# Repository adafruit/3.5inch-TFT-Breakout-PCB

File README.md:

# Adafruit 3.5 inch TFT LCD Display Breakout PCB

<a href="http://www.adafruit.com/products/2050"><br/>
Click here to purchase one from the Adafruit shop</a>

<a href="http://www.adafruit.com/products/5846"><br/>
Click here to purchase one from the Adafruit shop</a>

Adafruit 3.5" 18-bit color TFT LCD display with microSD card breakout

This TFT display is big (3.5" diagonal) bright (6 white-LED backlight) and colorful! 480x320 pixels with individual RGB pixel control, this has way more resolution than a black and white 128x64 display, and double our 2.8" TFT. 

There are two version of this display: one has a resistive touchscreen attached to it and the other has a capacitive touchscreen attached.

This display has a controller built into it with RAM buffering, so that almost no work is done by the microcontroller. The display can be used in two modes: 8-bit or SPI. For 8-bit mode, you'll need 8 digital data lines and 4 or 5 digital control lines to read and write to the display (12 lines total). SPI mode requires only 5 pins total (SPI data in, data out, clock, select, and d/c) but is slower than 8-bit mode. In addition, 4 pins are required for the touch screen (2 digital, 2 analog) or you can purchase and use our resistive touchscreen controller (not included) to use I2C or SPI.

These are the Eagle CAD files for the Adafruit 3.5" 18-bit color TFT LCD display with microSD card breakout:
  ----> https://www.adafruit.com/products/2050

and the Adafruit 3.5" TFT 320x480 with Capacitive Touch Breakout Board - EYESPI
  ----> https://www.adafruit.com/products/5846

### License

Adafruit invests time and resources providing this open source design, please support Adafruit and open-source hardware by purchasing products from [Adafruit](https://www.adafruit.com)!

All text above must be included in any redistribution

Designed by Limor Fried/Ladyada for Adafruit Industries.
Creative Commons Attribution/Share-Alike, all text above must be included in any redistribution. 
See license.txt for additional information.

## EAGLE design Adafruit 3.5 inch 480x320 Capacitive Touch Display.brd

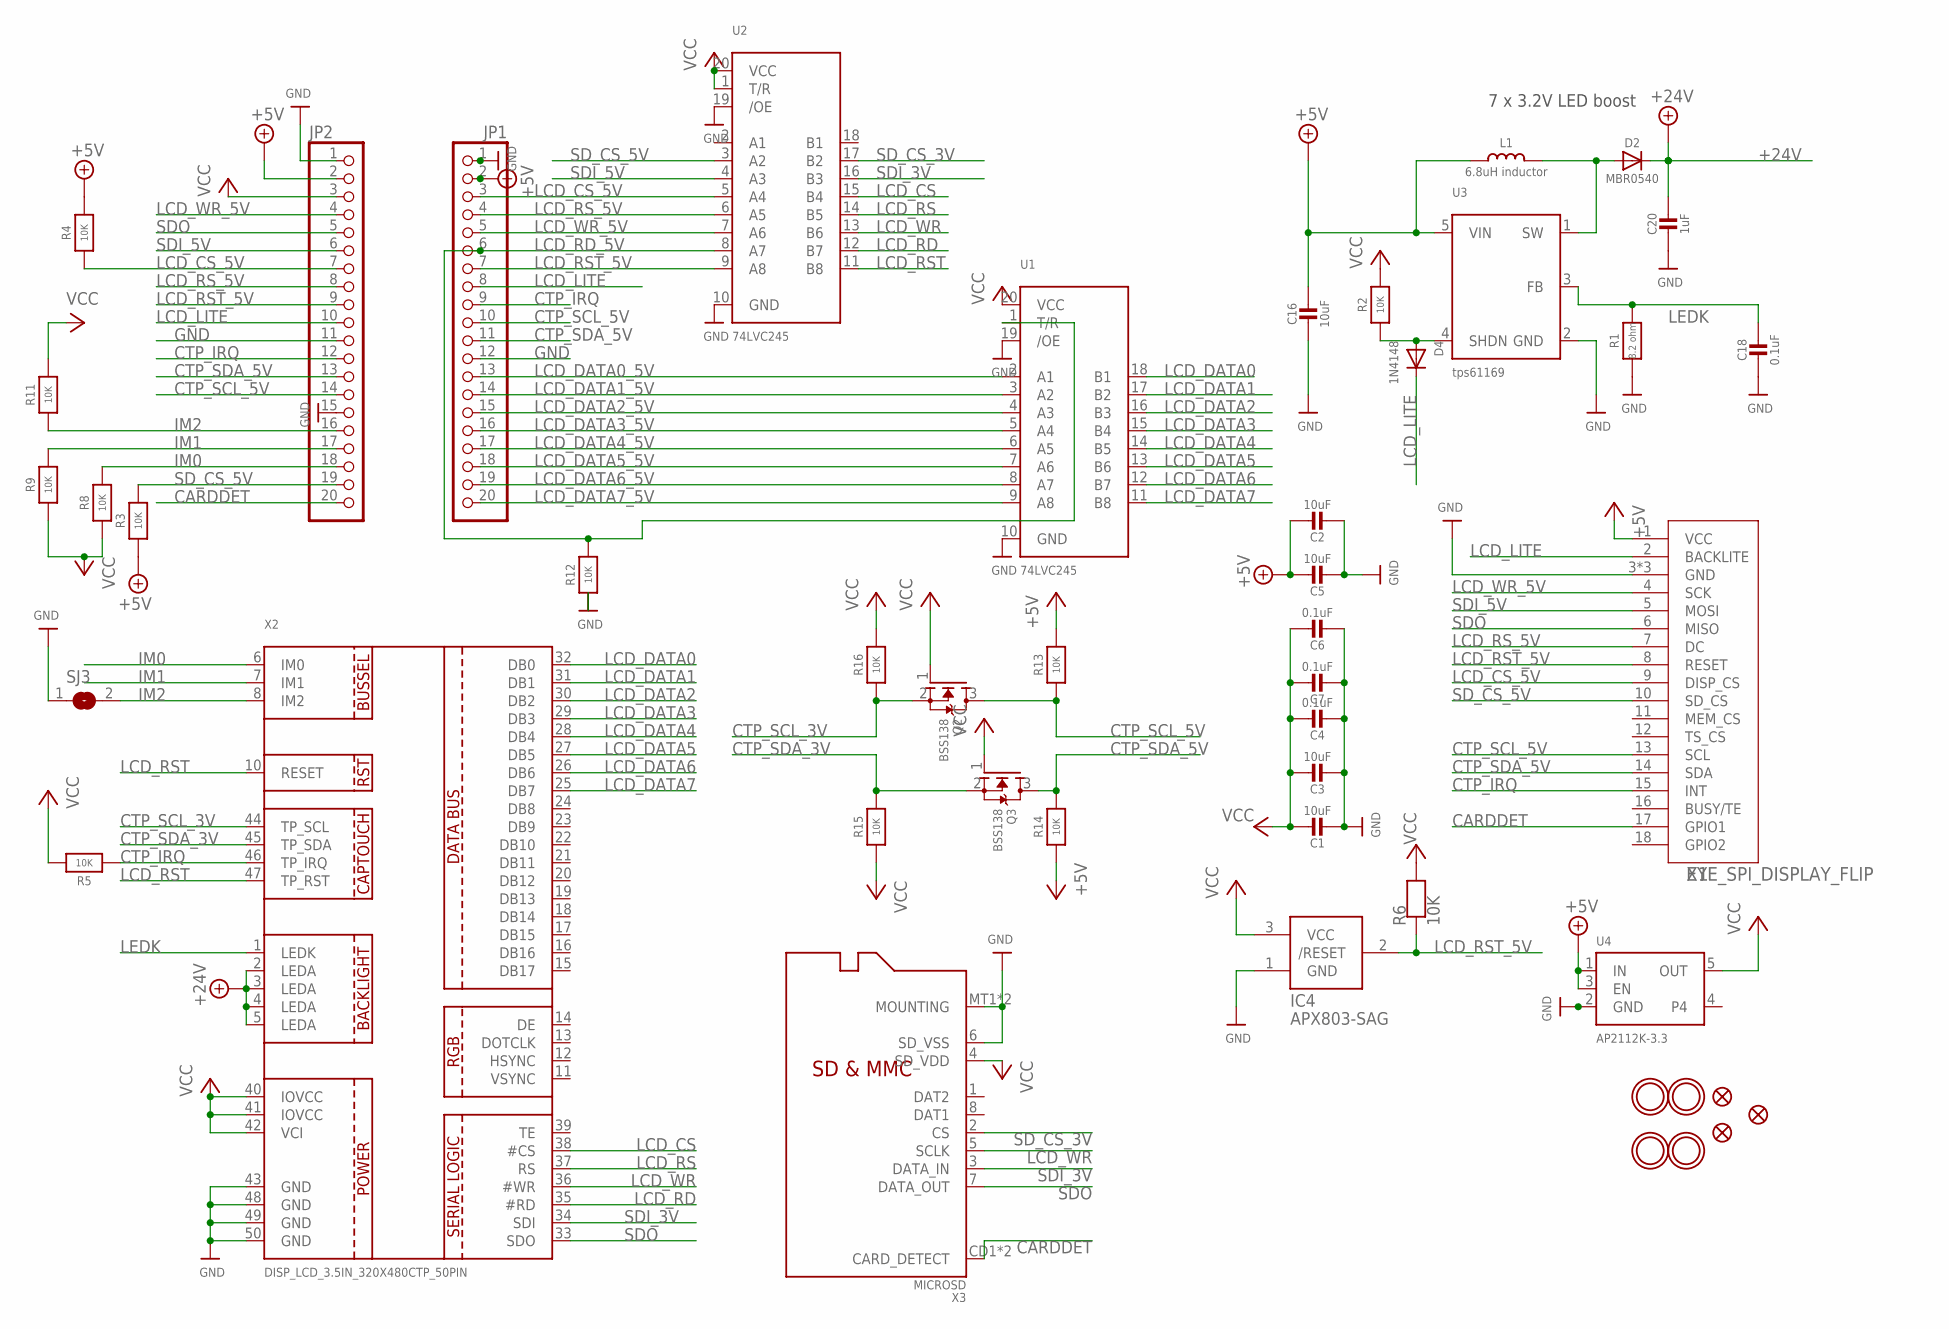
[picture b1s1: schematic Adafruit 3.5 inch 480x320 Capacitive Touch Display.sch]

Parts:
C1, C2, C3, C5, C16: 10uF; 0805-NO
C4, C6, C7, C18: 0.1uF; 0603-NO
C20: 1uF; 0805-NO
D2: MBR0540; SOD-123
D4: 1N4148; SOD-323F
IC4: APX803-SAG; SOT23
JP1, JP2: HEADER-1X20ROUND; 1X20_ROUND
L1: 6.8uH inductor; INDUCTOR_5X5MM_NR5040_NOTHERMALS
Q2, Q3: BSS138; SOT23-WIDE
R1: 8.2 ohm; 0603-NO
R2, R3, R4, R5, R6, R8, R9, R11, R12, R13, R14, R15, R16: 10K; 0603-NO
SJ3: SOLDERJUMPER; SOLDERJUMPER_ARROW_NOPASTE
U1, U2: 74LVC245; TSSOP20
U3: tps61169; SC70-5
U4: AP2112K-3.3; SOT23-5
U$7, U$15, U$16, U$17: MOUNTINGHOLE3.0THIN; MOUNTINGHOLE_3.0_PLATEDTHIN
U$9, U$11, U$23: FIDUCIAL_1MM
X1: EYE_SPI_DISPLAY_FLIP; EYE_SPI_DISPLAY_BOTCONTACT
X2: DISP_LCD_3.5IN_320X480CTP_50PIN; TFT_3.5IN_320X480_50PIN
X3: MICROSD

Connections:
+5V: C2.1, C5.1, C16.1, JP1.2, JP2.2, L1.P$1 (1), R3.1, R4.2, R13.2, R14.1, U3.5 (VIN), U4.1 (IN), U4.3 (EN), X1.1 (VCC)
+24V: C20.1, D2.C, X2.2 (LEDA), X2.3 (LEDA), X2.4 (LEDA), X2.5 (LEDA)
CARDDET: JP2.20, X1.17 (GPIO1), X3.CD1 (CARD_DETECT), X3.CD2 (CARD_DETECT)
CTP_IRQ: JP1.9, JP2.12, R5.1, X1.15 (INT), X2.46 (TP_IRQ)
CTP_SCL_3V: Q2.2 (S), R16.1, X2.44 (TP_SCL)
CTP_SCL_5V: JP1.10, JP2.14, Q2.3 (D), R13.1, X1.13 (SCL)
CTP_SDA_3V: Q3.2 (S), R15.2, X2.45 (TP_SDA)
CTP_SDA_5V: JP1.11, JP2.13, Q3.3 (D), R14.2, X1.14 (SDA)
GND: C1.2, C2.2, C3.2, C4.2, C5.2, C6.2, C7.2, C16.2, C18.2, C20.2, IC4.1 (GND), JP1.1, JP1.12, JP2.1, JP2.11, JP2.15, R1.1, R12.1, SJ3.1, U1.10 (GND), U1.19 (/OE), U2.10 (GND), U2.19 (/OE), U3.2 (GND), U4.2 (GND), X1.3 (GND), X1.SUPPORT1 (GND), X1.SUPPORT2 (GND), X2.43 (GND), X2.48 (GND), X2.49 (GND), X2.50 (GND), X3.6 (SD_VSS), X3.MT1 (MOUNTING), X3.MT2 (MOUNTING)
IM0: JP2.18, R8.2, X2.6 (IM0)
IM1: JP2.17, R9.2, X2.7 (IM1)
IM2: JP2.16, R11.1, SJ3.2, X2.8 (IM2)
LCD_CS: U2.15 (B4), X2.38 (#CS)
LCD_CS_5V: JP1.3, JP2.7, R4.1, U2.5 (A4), X1.9 (DISP_CS)
LCD_DATA0: U1.18 (B1), X2.32 (DB0)
LCD_DATA0_5V: JP1.13, U1.2 (A1)
LCD_DATA1: U1.17 (B2), X2.31 (DB1)
LCD_DATA1_5V: JP1.14, U1.3 (A2)
LCD_DATA2: U1.16 (B3), X2.30 (DB2)
LCD_DATA2_5V: JP1.15, U1.4 (A3)
LCD_DATA3: U1.15 (B4), X2.29 (DB3)
LCD_DATA3_5V: JP1.16, U1.5 (A4)
LCD_DATA4: U1.14 (B5), X2.28 (DB4)
LCD_DATA4_5V: JP1.17, U1.6 (A5)
LCD_DATA5: U1.13 (B6), X2.27 (DB5)
LCD_DATA5_5V: JP1.18, U1.7 (A6)
LCD_DATA6: U1.12 (B7), X2.26 (DB6)
LCD_DATA6_5V: JP1.19, U1.8 (A7)
LCD_DATA7: U1.11 (B8), X2.25 (DB7)
LCD_DATA7_5V: JP1.20, U1.9 (A8)
LCD_LITE: D4.C, JP1.8, JP2.10, X1.2 (BACKLITE)
LCD_RD: U2.12 (B7), X2.35 (#RD)
LCD_RD_5V: JP1.6, R12.2, U1.1 (T/R), U2.8 (A7)
LCD_RS: U2.14 (B5), X2.37 (RS)
LCD_RST: U2.11 (B8), X2.10 (RESET), X2.47 (TP_RST)
LCD_RST_5V: IC4.2 (/RESET), JP1.7, JP2.9, R6.1, U2.9 (A8), X1.8 (RESET)
LCD_RS_5V: JP1.4, JP2.8, U2.6 (A5), X1.7 (DC)
LCD_WR: U2.13 (B6), X2.36 (#WR), X3.5 (SCLK)
LCD_WR_5V: JP1.5, JP2.4, U2.7 (A6), X1.4 (SCK)
LEDK: C18.1, R1.2, U3.3 (FB), X2.1 (LEDK)
unnamed: D2.A, L1.P$2 (2), U3.1 (SW)
SDI_3V: U2.16 (B3), X2.34 (SDI), X3.3 (DATA_IN)
SDI_5V: JP2.6, U2.4 (A3), X1.5 (MOSI)
SDO: JP2.5, X1.6 (MISO), X2.33 (SDO), X3.7 (DATA_OUT)
SD_CS_3V: U2.17 (B2), X3.2 (CS)
SD_CS_5V: JP2.19, R3.2, U2.3 (A2), X1.10 (SD_CS)
SHDN: D4.A, R2.1, U3.4 (SHDN)
VCC: C1.1, C3.1, C4.1, C6.1, C7.1, IC4.3 (VCC), JP2.3, Q2.1 (G), Q3.1 (G), R2.2, R5.2, R6.2, R8.1, R9.1, R11.2, R15.1, R16.2, U1.20 (VCC), U2.1 (T/R), U2.20 (VCC), U4.5 (OUT), X2.40 (IOVCC), X2.41 (IOVCC), X2.42 (VCI), X3.4 (SD_VDD)

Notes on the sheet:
7 x 3.2V LED boost

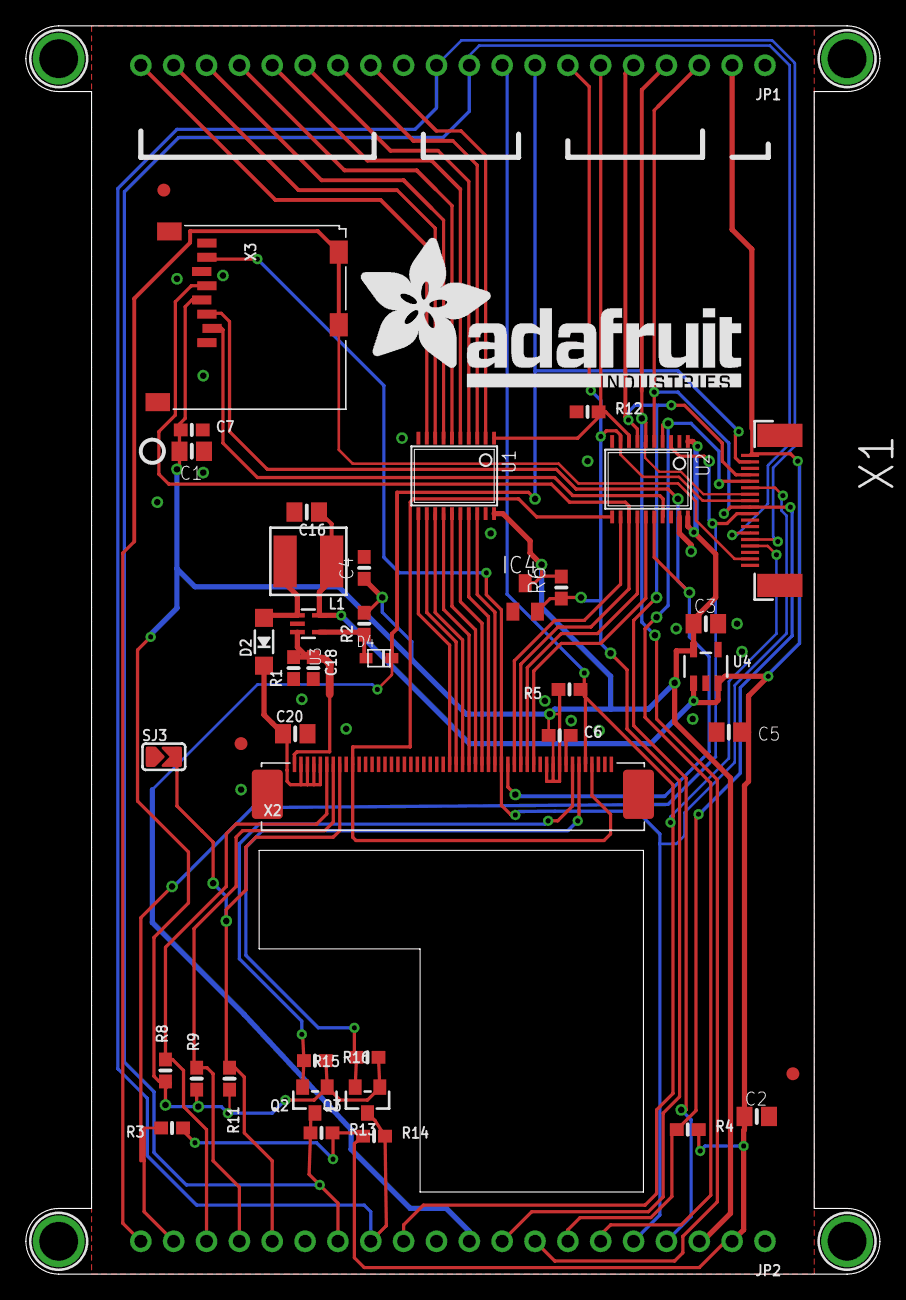
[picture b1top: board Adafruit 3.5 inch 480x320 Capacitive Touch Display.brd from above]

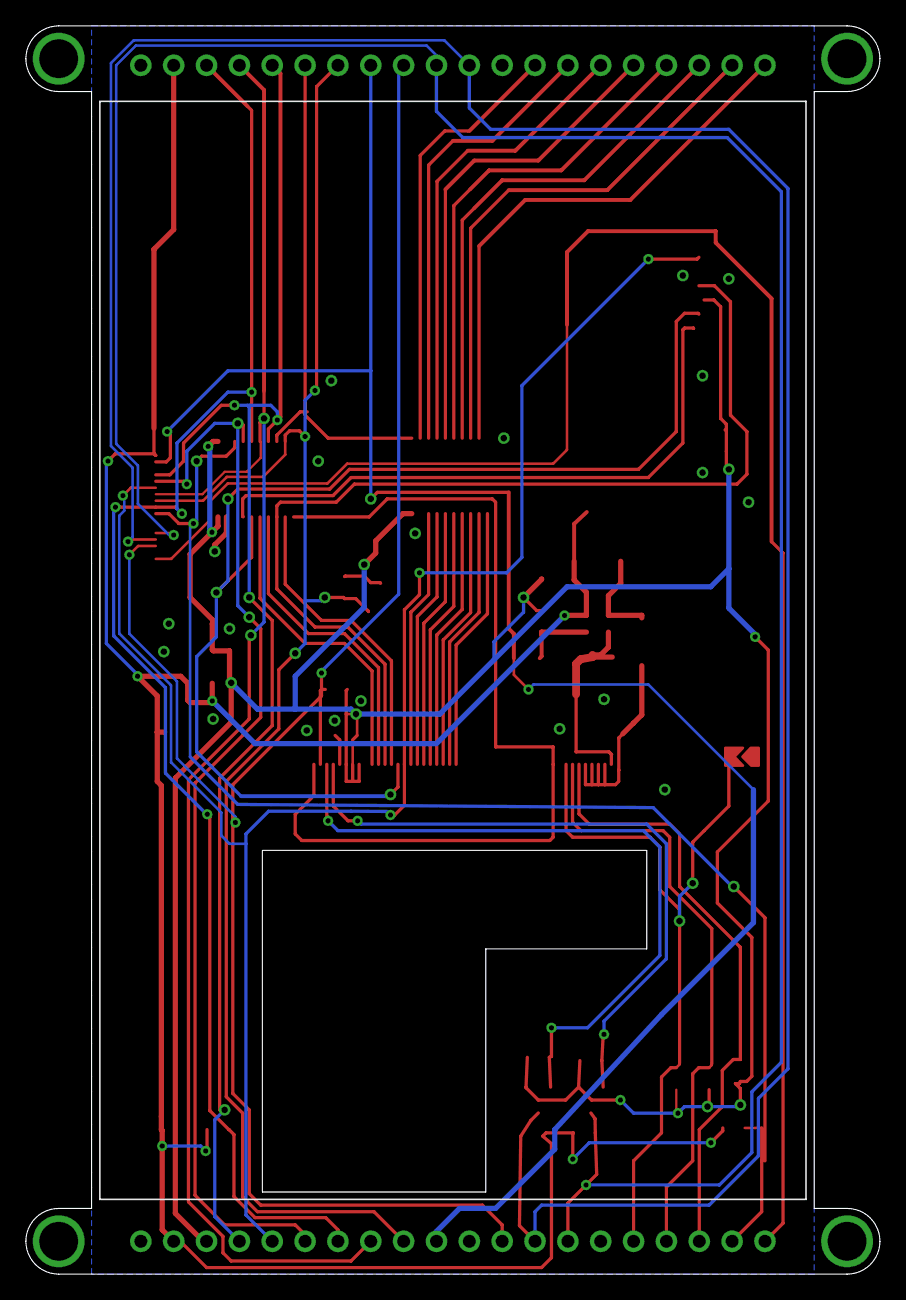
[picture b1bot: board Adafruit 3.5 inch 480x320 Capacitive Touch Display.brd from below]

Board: 2 copper layers, 66.0 x 96.5 mm, 143 parts (41 on the bottom side), 48 nets.

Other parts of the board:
PLABEL0: PLABEL0
PLABEL1: PLABEL1
PLABEL2: PLABEL2
PLABEL3: PLABEL3
PLABEL4: PLABEL4
PLABEL5: PLABEL5
PLABEL6: PLABEL6
PLABEL7: PLABEL7
PLABEL8: PLABEL8
PLABEL9: PLABEL9
PLABEL10: PLABEL10
PLABEL11: PLABEL11
PLABEL12: PLABEL12
PLABEL13: PLABEL13
PLABEL14: PLABEL14
PLABEL15: PLABEL15
PLABEL16: PLABEL16
PLABEL17: PLABEL17
PLABEL18: PLABEL18
PLABEL19: PLABEL19
PLABEL20: PLABEL20
PLABEL21: PLABEL21
PLABEL22: PLABEL22
PLABEL23: PLABEL23
PLABEL24: PLABEL24
PLABEL25: PLABEL25
PLABEL26: PLABEL26
PLABEL27: PLABEL27
PLABEL28: PLABEL28
PLABEL29: PLABEL29
PLABEL30: PLABEL30
PLABEL31: PLABEL31
PLABEL32: PLABEL32
PLABEL33: PLABEL33
PLABEL34: PLABEL34
PLABEL35: PLABEL35
PLABEL36: PLABEL36
PLABEL37: PLABEL37
PLABEL38: PLABEL38
PLABEL39: PLABEL39
PLABEL40: PLABEL40
PLABEL41: PLABEL41
PLABEL42: PLABEL42
PLABEL43: PLABEL43
PLABEL44: PLABEL44
PLABEL45: PLABEL45
PLABEL46: PLABEL46
PLABEL47: PLABEL47
PLABEL48: PLABEL48
PLABEL49: PLABEL49
PLABEL50: PLABEL50
PLABEL51: PLABEL51
PLABEL52: PLABEL52
PLABEL53: PLABEL53
PLABEL54: PLABEL54
PLABEL55: PLABEL55
PLABEL56: PLABEL56
PLABEL57: PLABEL57
PLABEL58: PLABEL58
PLABEL59: PLABEL59
PLABEL60: PLABEL60
PLABEL61: PLABEL61
PLABEL62: PLABEL62
PLABEL63: PLABEL63
PLABEL64: PLABEL64
PLABEL65: PLABEL65
PLABEL66: PLABEL66
PLABEL67: PLABEL67
PLABEL68: PLABEL68
PLABEL69: PLABEL69
PLABEL70: PLABEL70
PLABEL71: PLABEL71
PLABEL72: PLABEL72
PLABEL73: PLABEL73
PLABEL74: PLABEL74
PLABEL75: PLABEL75
PLABEL76: PLABEL76
PLABEL77: PLABEL77
PLABEL78: PLABEL78
PLABEL79: PLABEL79
PLABEL80: PLABEL80
PLABEL81: PLABEL81
PLABEL82: PLABEL82
PLABEL83: PLABEL83
PLABEL84: PLABEL84
PLABEL85: PLABEL85
PLABEL86: PLABEL86
PLABEL87: PLABEL87
PLABEL88: PLABEL88
PLABEL89: PLABEL89
PLABEL90: PLABEL90
PLABEL91: PLABEL91
PLABEL92: PLABEL92
PLABEL93: PLABEL93
U$19: ADAFRUIT_TEXT_30MM
U$31: PCBFEAT-REV-040

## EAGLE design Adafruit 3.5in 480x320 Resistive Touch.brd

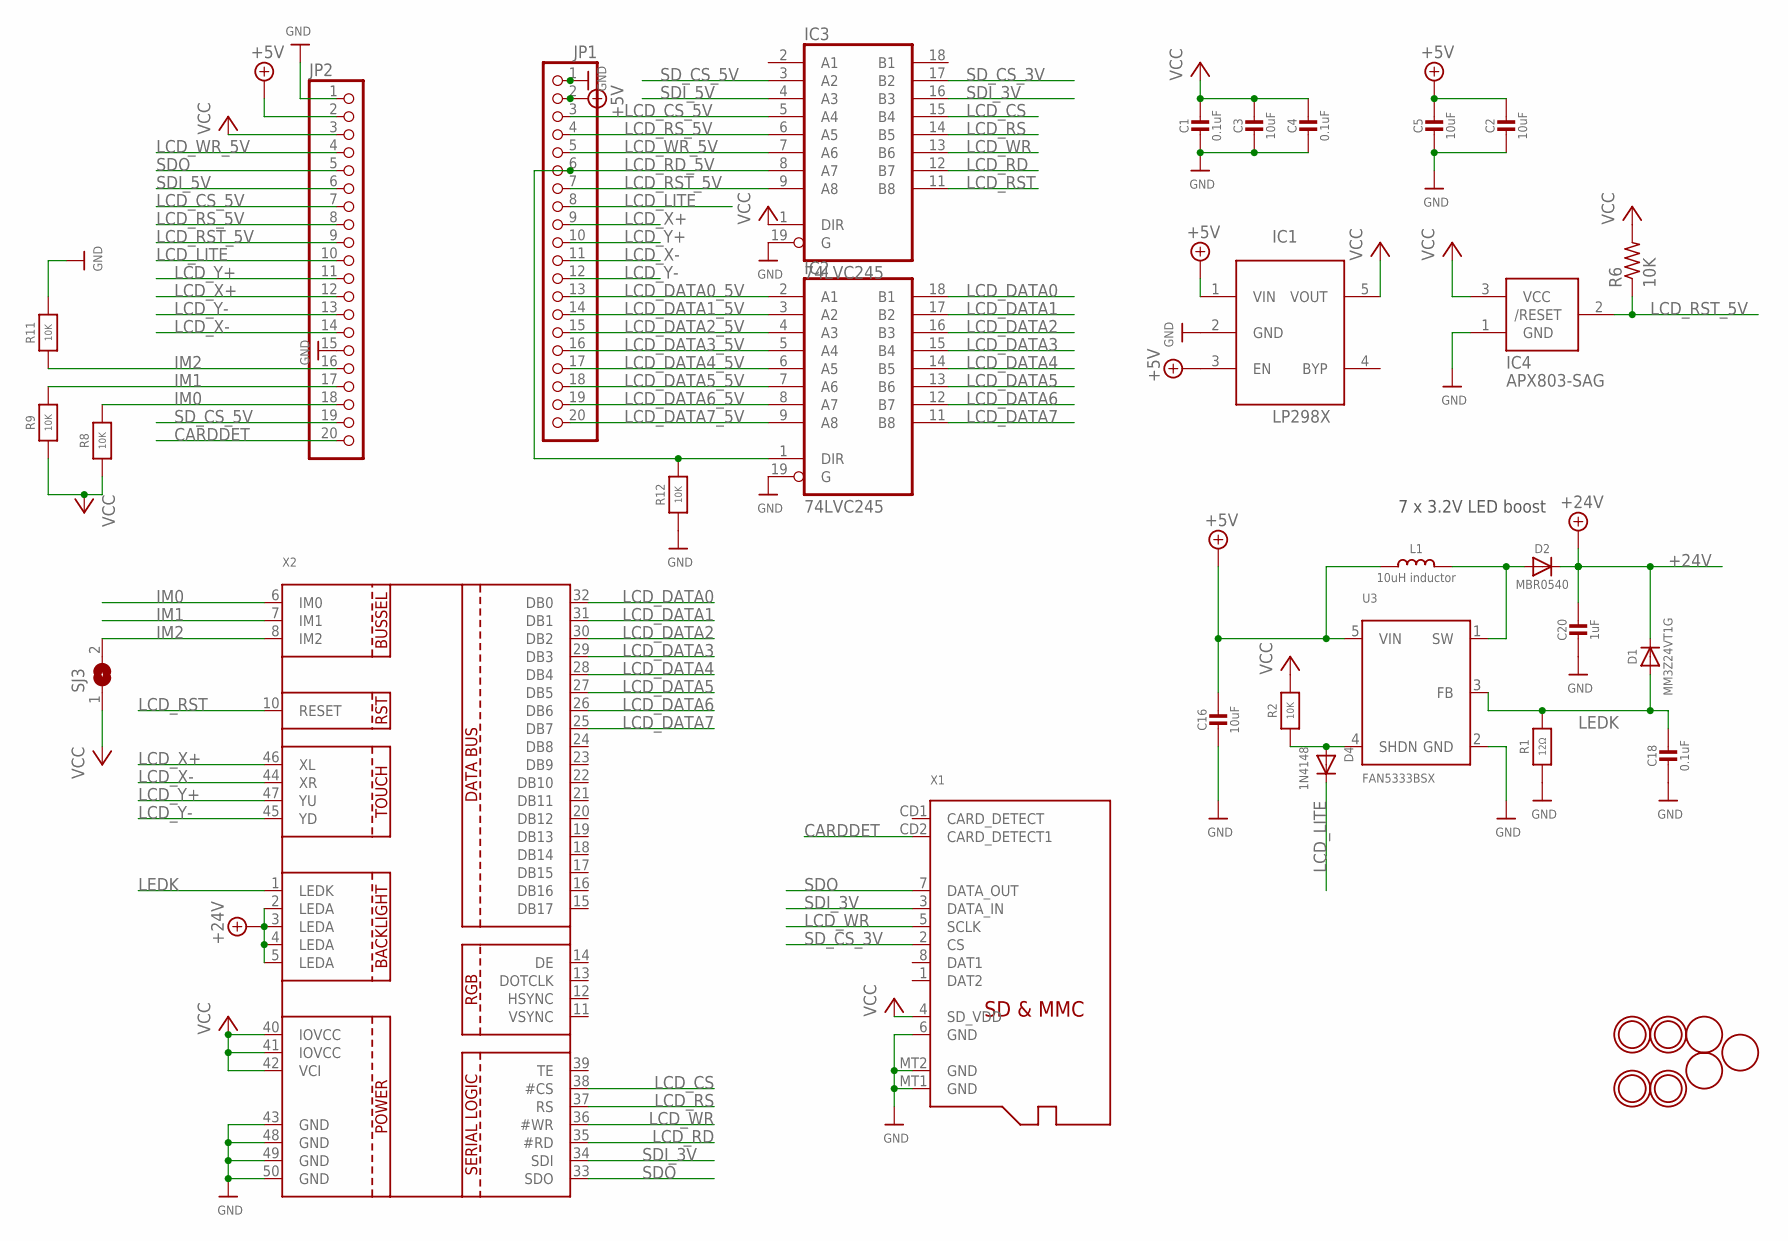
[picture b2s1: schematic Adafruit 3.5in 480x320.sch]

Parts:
C1, C4, C18: 0.1uF; 0805-NO
C2, C3, C5: 10uF; 0805-NO
C16: 10uF; _0805MP
C20: 1uF; 0805-NO
D1: MM3Z24VT1G; SMADIODE
D2: MBR0540; SOD-123
D4: 1N4148; SOD-323F
IC1: MIC5225-3.3; SOT23-5L
IC2, IC3: 74LVC245; SO20W
IC4: APX803-SAG; SOT23
JP1, JP2: HEADER-1X20ROUND; 1X20_ROUND
L1: 10uH inductor; INDUCTOR_5X5MM_NR5040_NOTHERMALS
R1: 12Ω; _0805MP
R2, R8, R9, R11, R12: 10K; 0805-NO
R6: 10K; R0805
SJ3: SOLDERJUMPER; SOLDERJUMPER_ARROW_NOPASTE
U3: FAN5333BSX; SOT23-5@1
U$7, U$15, U$16, U$17: MOUNTINGHOLE3.0THIN; MOUNTINGHOLE_3.0_PLATEDTHIN
U$9, U$11, U$23: FIDUCIAL; FIDUCIAL_1MM
X1: MICROSD
X2: DISP_LCD_3.5IN_320X480_50PIN; TFT_3.5IN_320X480_50PIN

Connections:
+5V: C2.1, C5.1, C16.1, IC1.1 (VIN), IC1.3 (EN), JP1.2, JP2.2, L1.P$1 (1), U3.5 (VIN)
+24V: C20.1, D1.C, D2.C, X2.2 (LEDA), X2.3 (LEDA), X2.4 (LEDA), X2.5 (LEDA)
CARDDET: JP2.20, X1.CD2 (CARD_DETECT1)
GND: C1.2, C2.2, C3.2, C4.2, C5.2, C16.2, C18.2, C20.2, IC1.2 (GND), IC2.10 (GND), IC2.19 (G), IC3.10 (GND), IC3.19 (G), IC4.1 (GND), JP1.1, JP2.1, JP2.15, R1.1, R11.2, R12.1, U3.2 (GND), X1.6 (GND), X1.MT1 (GND), X1.MT2 (GND), X2.43 (GND), X2.48 (GND), X2.49 (GND), X2.50 (GND)
IM0: JP2.18, R8.2, X2.6 (IM0)
IM1: JP2.17, R9.2, X2.7 (IM1)
IM2: JP2.16, R11.1, SJ3.2, X2.8 (IM2)
LCD_CS: IC3.15 (B4), X2.38 (#CS)
LCD_CS_5V: IC3.5 (A4), JP1.3, JP2.7
LCD_DATA0: IC2.18 (B1), X2.32 (DB0)
LCD_DATA0_5V: IC2.2 (A1), JP1.13
LCD_DATA1: IC2.17 (B2), X2.31 (DB1)
LCD_DATA1_5V: IC2.3 (A2), JP1.14
LCD_DATA2: IC2.16 (B3), X2.30 (DB2)
LCD_DATA2_5V: IC2.4 (A3), JP1.15
LCD_DATA3: IC2.15 (B4), X2.29 (DB3)
LCD_DATA3_5V: IC2.5 (A4), JP1.16
LCD_DATA4: IC2.14 (B5), X2.28 (DB4)
LCD_DATA4_5V: IC2.6 (A5), JP1.17
LCD_DATA5: IC2.13 (B6), X2.27 (DB5)
LCD_DATA5_5V: IC2.7 (A6), JP1.18
LCD_DATA6: IC2.12 (B7), X2.26 (DB6)
LCD_DATA6_5V: IC2.8 (A7), JP1.19
LCD_DATA7: IC2.11 (B8), X2.25 (DB7)
LCD_DATA7_5V: IC2.9 (A8), JP1.20
LCD_LITE: D4.C, JP1.8, JP2.10
LCD_RD: IC3.12 (B7), X2.35 (#RD)
LCD_RD_5V: IC2.1 (DIR), IC3.8 (A7), JP1.6, R12.2
LCD_RS: IC3.14 (B5), X2.37 (RS)
LCD_RST: IC3.11 (B8), X2.10 (RESET)
LCD_RST_5V: IC3.9 (A8), IC4.2 (/RESET), JP1.7, JP2.9, R6.1
LCD_RS_5V: IC3.6 (A5), JP1.4, JP2.8
LCD_WR: IC3.13 (B6), X1.5 (SCLK), X2.36 (#WR)
LCD_WR_5V: IC3.7 (A6), JP1.5, JP2.4
LCD_X+: JP1.9, JP2.12, X2.46 (XL)
LCD_X-: JP1.11, JP2.14, X2.44 (XR)
LCD_Y+: JP1.10, JP2.11, X2.47 (YU)
LCD_Y-: JP1.12, JP2.13, X2.45 (YD)
LEDK: C18.1, D1.A, R1.2, U3.3 (FB), X2.1 (LEDK)
unnamed: D2.A, L1.P$2 (2), U3.1 (SW)
SDI_3V: IC3.16 (B3), X1.3 (DATA_IN), X2.34 (SDI)
SDI_5V: IC3.4 (A3), JP2.6
SDO: JP2.5, X1.7 (DATA_OUT), X2.33 (SDO)
SD_CS_3V: IC3.17 (B2), X1.2 (CS)
SD_CS_5V: IC3.3 (A2), JP2.19
SHDN: D4.A, R2.1, U3.4 (SHDN)
VCC: C1.1, C3.1, C4.1, IC1.5 (VOUT), IC2.20 (VCC), IC3.1 (DIR), IC3.20 (VCC), IC4.3 (VCC), JP2.3, R2.2, R6.2, R8.1, R9.1, SJ3.1, X1.4 (SD_VDD), X2.40 (IOVCC), X2.41 (IOVCC), X2.42 (VCI)

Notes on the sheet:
7 x 3.2V LED boost

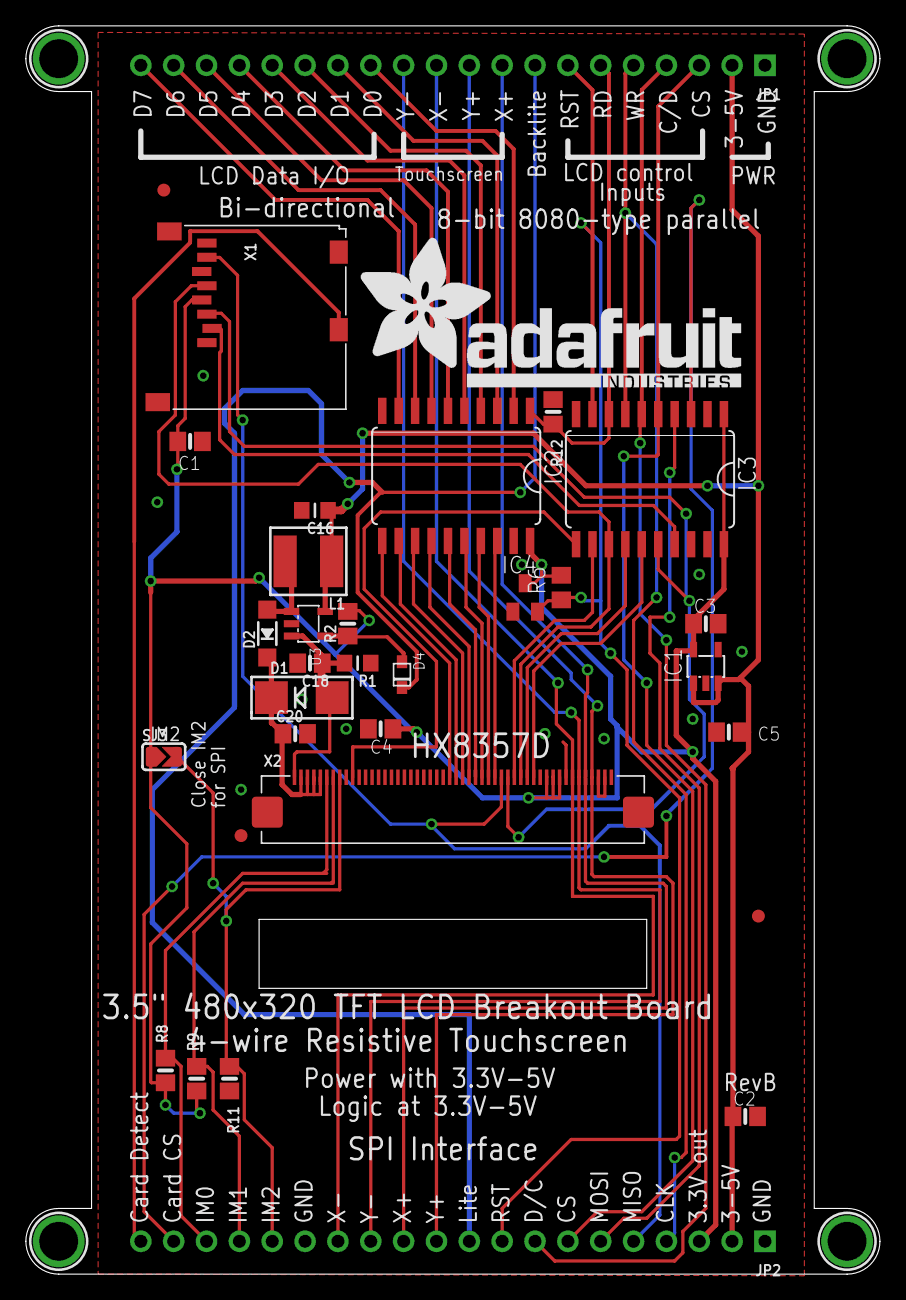
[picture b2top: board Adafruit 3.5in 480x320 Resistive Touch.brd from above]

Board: 2 copper layers, 66.0 x 96.5 mm, 37 parts (1 on the bottom side), 47 nets.

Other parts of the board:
U$19: ADAFRUIT_TEXT_30MM

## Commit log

2015-02-01 init
2015-02-01 url and such
2023-11-28 cap touch
